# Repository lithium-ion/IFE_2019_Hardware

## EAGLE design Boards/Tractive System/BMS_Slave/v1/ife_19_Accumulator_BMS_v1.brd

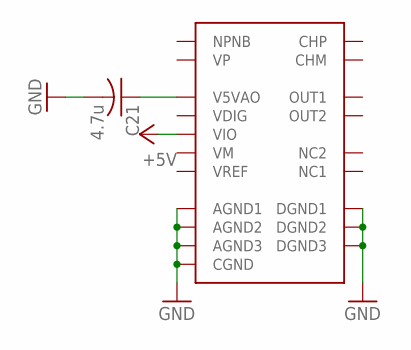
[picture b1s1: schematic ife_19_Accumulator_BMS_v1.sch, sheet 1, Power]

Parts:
C21: 4.7u; C0805
U$1: BQ76PL455A; TQFP80

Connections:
+5V: U$1.41 (VIO); also elsewhere on the board
GND: C21.2, U$1.30 (DGND1), U$1.35 (DGND2), U$1.37 (DGND3), U$1.48 (CGND), U$1.69 (AGND3), U$1.72 (AGND2), U$1.74 (AGND1); also elsewhere on the board
unnamed: C21.1, U$1.58 (V5VAO)

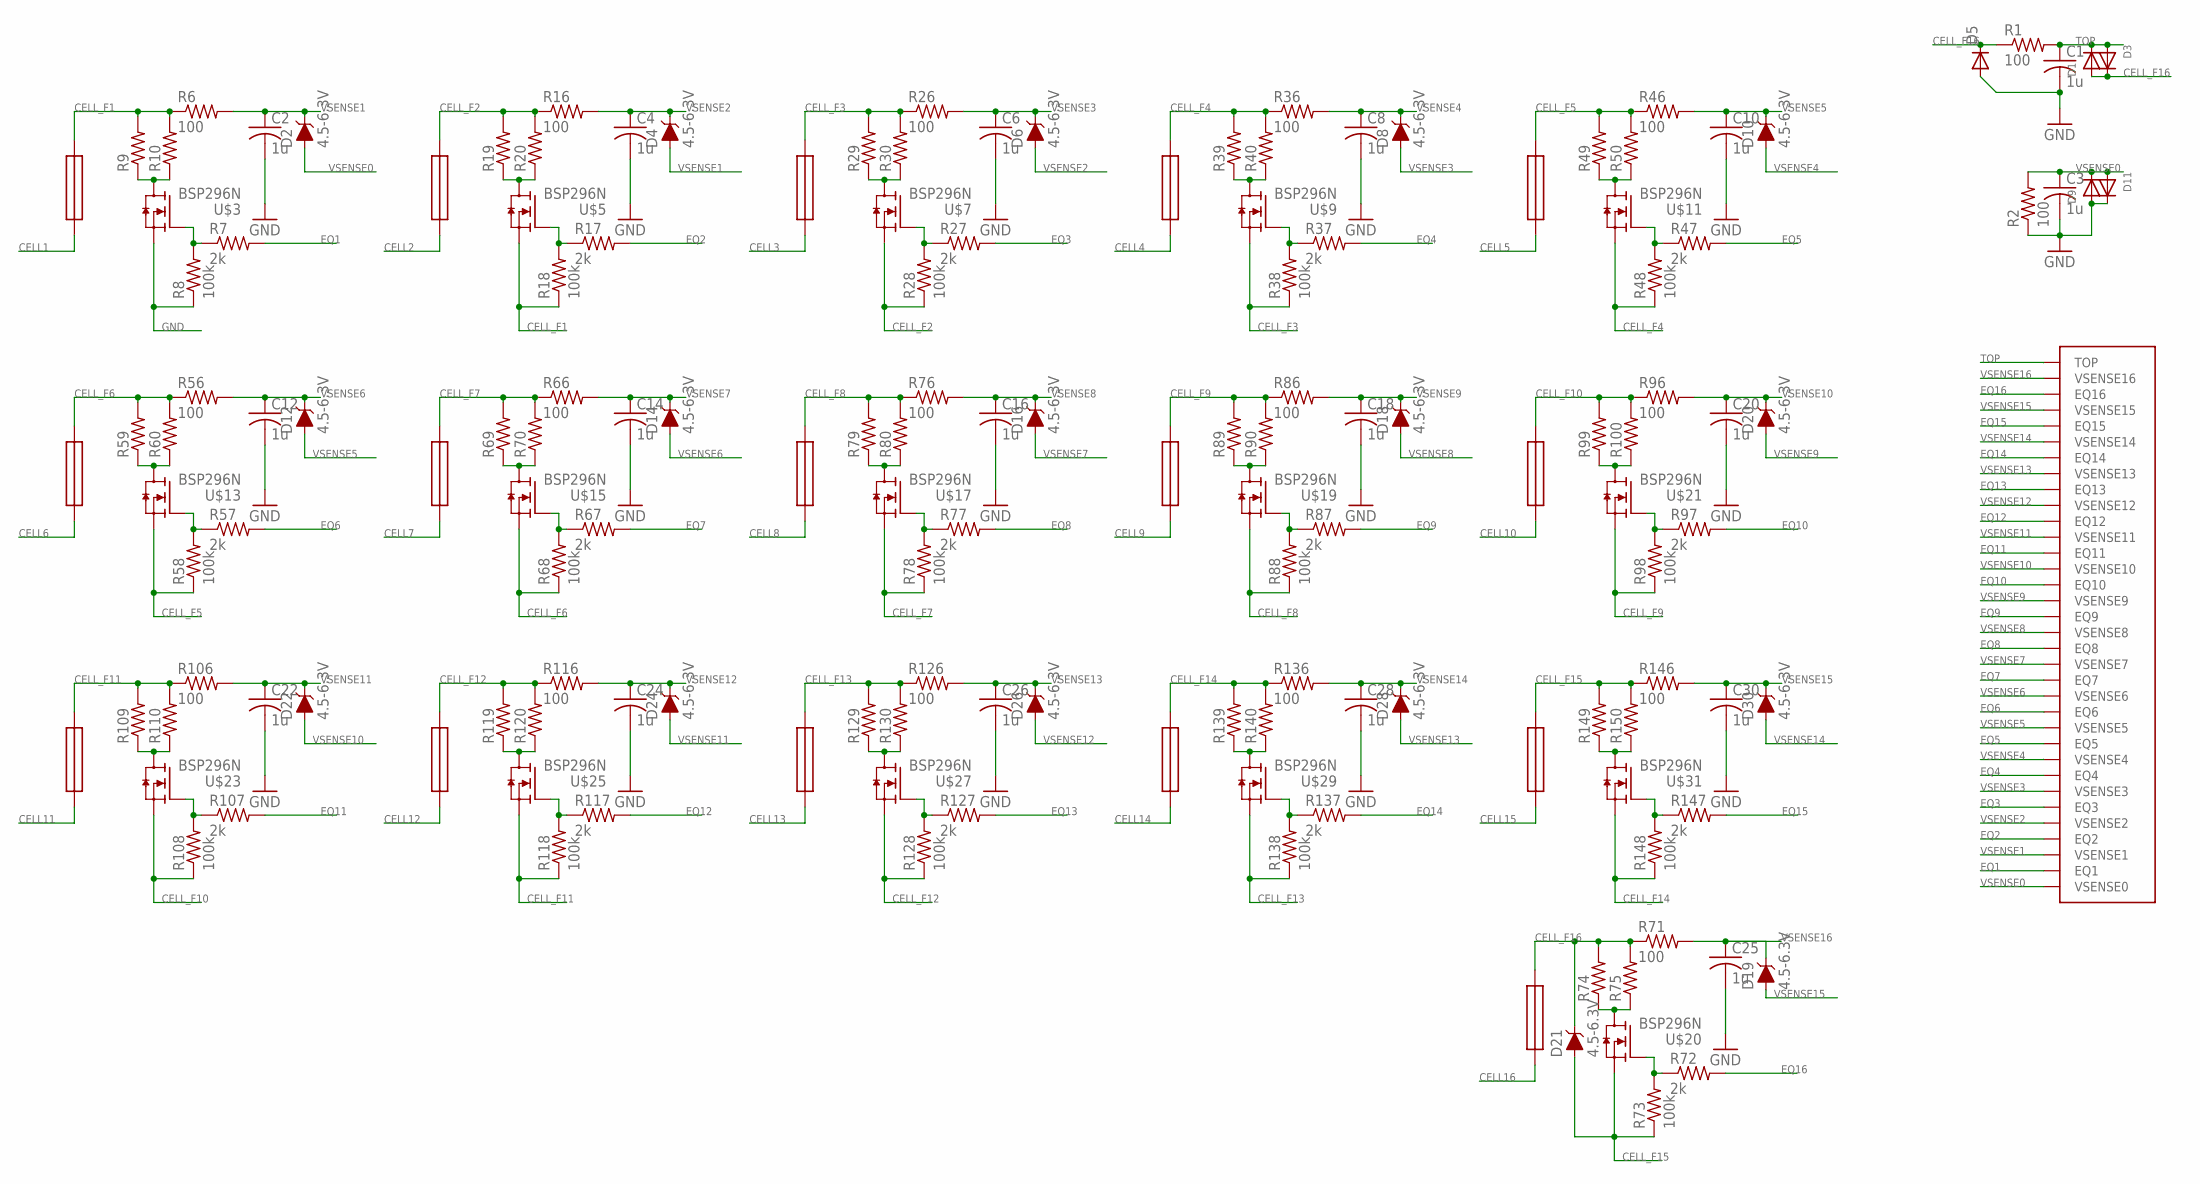
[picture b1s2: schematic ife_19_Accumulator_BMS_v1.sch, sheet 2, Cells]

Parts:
C1, C2, C3, C4, C6, C8, C10, C12, C14, C16, C18, C20, C22, C24, C25, C26, C28, C30: 1u; C0603K
D1, D3, D9, D11: DIODESOD-123; SOD-123
D2, D4, D6, D8, D10, D12, D14, D16, D18, D19, D20, D21, D22, D24, D26, D28, D30: 4.5-6.3V; SOD-323
D5: DIODE-DO214AC; DO214AC
FUSE1, FUSE2, FUSE3, FUSE5, FUSE7, FUSE9, FUSE11, FUSE13, FUSE15, FUSE17, FUSE19, FUSE21, FUSE23, FUSE25, FUSE27, FUSE29: 2A; 0.36"X0.15"
R1, R2, R6, R16, R26, R36, R46, R56, R66, R71, R76, R86, R96, R106, R116, R126, R136, R146: 100; R0603
R7, R17, R27, R37, R47, R57, R67, R72, R77, R87, R97, R107, R117, R127, R137, R147: 2k; R0603
R8, R18, R28, R38, R48, R58, R68, R73, R78, R88, R98, R108, R118, R128, R138, R148: 100k; R0603
R9, R10, R19, R20, R29, R30, R39, R40, R49, R50, R59, R60, R69, R70, R74, R75, R79, R80, R89, R90, R99, R100, R109, R110, R119, R120, R129, R130, R139, R140, R149, R150: R-US_R2512; R2512
U$1: BQ76PL455A; TQFP80
U$3, U$5, U$7, U$9, U$11, U$13, U$15, U$17, U$19, U$20, U$21, U$23, U$25, U$27, U$29, U$31: BSP296N; PG-SOT-223

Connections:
CELL1: FUSE1.P$1
CELL2: FUSE3.P$1
CELL3: FUSE5.P$1
CELL4: FUSE7.P$1
CELL5: FUSE9.P$1
CELL6: FUSE11.P$1
CELL7: FUSE13.P$1
CELL8: FUSE15.P$1
CELL9: FUSE17.P$1
CELL10: FUSE19.P$1
CELL11: FUSE21.P$1
CELL12: FUSE23.P$1
CELL13: FUSE25.P$1
CELL14: FUSE27.P$1
CELL15: FUSE29.P$1
CELL16: FUSE2.P$1
CELL_F1: FUSE1.P$2, R6.1, R9.2, R10.2, R18.1, U$5.3 (S)
CELL_F2: FUSE3.P$2, R16.1, R19.2, R20.2, R28.1, U$7.3 (S)
CELL_F3: FUSE5.P$2, R26.1, R29.2, R30.2, R38.1, U$9.3 (S)
CELL_F4: FUSE7.P$2, R36.1, R39.2, R40.2, R48.1, U$11.3 (S)
CELL_F5: FUSE9.P$2, R46.1, R49.2, R50.2, R58.1, U$13.3 (S)
CELL_F6: FUSE11.P$2, R56.1, R59.2, R60.2, R68.1, U$15.3 (S)
CELL_F7: FUSE13.P$2, R66.1, R69.2, R70.2, R78.1, U$17.3 (S)
CELL_F8: FUSE15.P$2, R76.1, R79.2, R80.2, R88.1, U$19.3 (S)
CELL_F9: FUSE17.P$2, R86.1, R89.2, R90.2, R98.1, U$21.3 (S)
CELL_F10: FUSE19.P$2, R96.1, R99.2, R100.2, R108.1, U$23.3 (S)
CELL_F11: FUSE21.P$2, R106.1, R109.2, R110.2, R118.1, U$25.3 (S)
CELL_F12: FUSE23.P$2, R116.1, R119.2, R120.2, R128.1, U$27.3 (S)
CELL_F13: FUSE25.P$2, R126.1, R129.2, R130.2, R138.1, U$29.3 (S)
CELL_F14: FUSE27.P$2, R136.1, R139.2, R140.2, R148.1, U$31.3 (S)
CELL_F15: D21.A, FUSE29.P$2, R73.1, R146.1, R149.2, R150.2, U$20.3 (S)
CELL_F16: D1.A, D3.C, D5.C, D21.C, FUSE2.P$2, R1.1, R71.1, R74.2, R75.2
EQ1: R7.2, U$1.28 (EQ1)
EQ2: R17.2, U$1.26 (EQ2)
EQ3: R27.2, U$1.24 (EQ3)
EQ4: R37.2, U$1.22 (EQ4)
EQ5: R47.2, U$1.20 (EQ5)
EQ6: R57.2, U$1.18 (EQ6)
EQ7: R67.2, U$1.16 (EQ7)
EQ8: R77.2, U$1.14 (EQ8)
EQ9: R87.2, U$1.12 (EQ9)
EQ10: R97.2, U$1.10 (EQ10)
EQ11: R107.2, U$1.8 (EQ11)
EQ12: R117.2, U$1.6 (EQ12)
EQ13: R127.2, U$1.4 (EQ13)
EQ14: R137.2, U$1.2 (EQ14)
EQ15: R147.2, U$1.80 (EQ15)
EQ16: R72.2, U$1.78 (EQ16)
GATE1: R7.1, R8.2, U$3.1 (G)
GATE2: R17.1, R18.2, U$5.1 (G)
GATE3: R27.1, R28.2, U$7.1 (G)
GATE4: R37.1, R38.2, U$9.1 (G)
GATE5: R47.1, R48.2, U$11.1 (G)
GATE6: R57.1, R58.2, U$13.1 (G)
GATE7: R67.1, R68.2, U$15.1 (G)
GATE8: R77.1, R78.2, U$17.1 (G)
GATE9: R87.1, R88.2, U$19.1 (G)
GATE10: R97.1, R98.2, U$21.1 (G)
GATE11: R107.1, R108.2, U$23.1 (G)
GATE12: R117.1, R118.2, U$25.1 (G)
GATE13: R127.1, R128.2, U$27.1 (G)
GATE14: R137.1, R138.2, U$29.1 (G)
GATE15: R147.1, R148.2, U$31.1 (G)
GATE16: R72.1, R73.2, U$20.1 (G)
GND: C1.2, C2.2, C3.2, C4.2, C6.2, C8.2, C10.2, C12.2, C14.2, C16.2, C18.2, C20.2, C22.2, C24.2, C25.2, C26.2, C28.2, C30.2, D5.A, D9.A, D11.C, R2.1, R8.1, U$3.3 (S); also elsewhere on the board
unnamed: R9.1, R10.1, U$3.2 (D), U$3.4 (D)
unnamed: R19.1, R20.1, U$5.2 (D), U$5.4 (D)
unnamed: R29.1, R30.1, U$7.2 (D), U$7.4 (D)
unnamed: R39.1, R40.1, U$9.2 (D), U$9.4 (D)
unnamed: R49.1, R50.1, U$11.2 (D), U$11.4 (D)
unnamed: R59.1, R60.1, U$13.2 (D), U$13.4 (D)
unnamed: R74.1, R75.1, U$20.2 (D), U$20.4 (D)
unnamed: R69.1, R70.1, U$15.2 (D), U$15.4 (D)
unnamed: R79.1, R80.1, U$17.2 (D), U$17.4 (D)
unnamed: R89.1, R90.1, U$19.2 (D), U$19.4 (D)
unnamed: R99.1, R100.1, U$21.2 (D), U$21.4 (D)
unnamed: R109.1, R110.1, U$23.2 (D), U$23.4 (D)
unnamed: R119.1, R120.1, U$25.2 (D), U$25.4 (D)
unnamed: R129.1, R130.1, U$27.2 (D), U$27.4 (D)
unnamed: R139.1, R140.1, U$29.2 (D), U$29.4 (D)
unnamed: R149.1, R150.1, U$31.2 (D), U$31.4 (D)
TOP: C1.1, D1.C, D3.A, R1.2, U$1.76 (TOP)
VSENSE0: C3.1, D2.A, D9.C, D11.A, R2.2, U$1.29 (VSENSE0)
VSENSE1: C2.1, D2.C, D4.A, R6.2, U$1.27 (VSENSE1)
VSENSE2: C4.1, D4.C, D6.A, R16.2, U$1.25 (VSENSE2)
VSENSE3: C6.1, D6.C, D8.A, R26.2, U$1.23 (VSENSE3)
VSENSE4: C8.1, D8.C, D10.A, R36.2, U$1.21 (VSENSE4)
VSENSE5: C10.1, D10.C, D12.A, R46.2, U$1.19 (VSENSE5)
VSENSE6: C12.1, D12.C, D14.A, R56.2, U$1.17 (VSENSE6)
VSENSE7: C14.1, D14.C, D16.A, R66.2, U$1.15 (VSENSE7)
VSENSE8: C16.1, D16.C, D18.A, R76.2, U$1.13 (VSENSE8)
VSENSE9: C18.1, D18.C, D20.A, R86.2, U$1.11 (VSENSE9)
VSENSE10: C20.1, D20.C, D22.A, R96.2, U$1.9 (VSENSE10)
VSENSE11: C22.1, D22.C, D24.A, R106.2, U$1.7 (VSENSE11)
VSENSE12: C24.1, D24.C, D26.A, R116.2, U$1.5 (VSENSE12)
VSENSE13: C26.1, D26.C, D28.A, R126.2, U$1.3 (VSENSE13)
VSENSE14: C28.1, D28.C, D30.A, R136.2, U$1.1 (VSENSE14)
VSENSE15: C30.1, D19.A, D30.C, R146.2, U$1.79 (VSENSE15)
VSENSE16: C25.1, D19.C, R71.2, U$1.77 (VSENSE16)

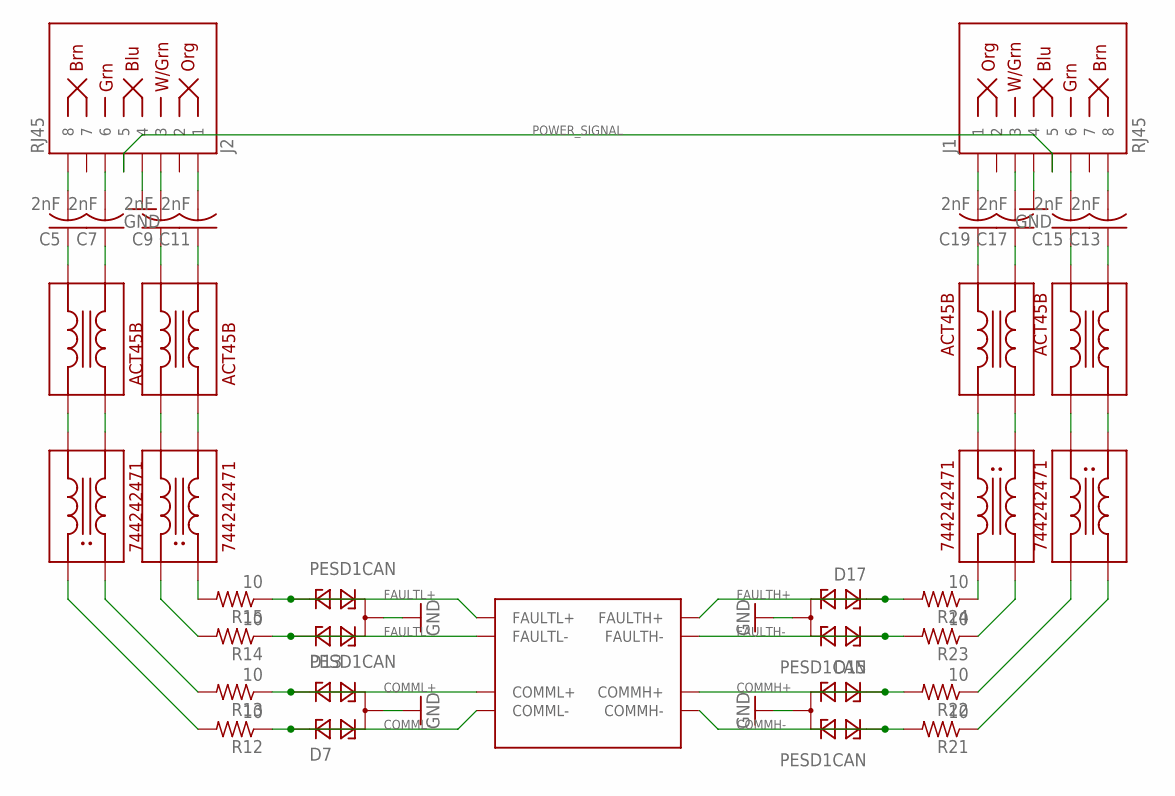
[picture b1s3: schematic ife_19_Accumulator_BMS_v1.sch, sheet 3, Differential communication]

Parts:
C5, C7, C9, C11, C13, C15, C17, C19: 2nF; C0805
D7, D13, D15, D17: PESD1CAN; SOT23
J1, J2: RJ45; RJ45-8
R12, R13, R14, R15, R21, R22, R23, R24: 10; R0805
U$1: BQ76PL455A; TQFP80
U$2, U$4, U$6, U$8: ACT45B; 1812-4
U$10, U$12, U$14, U$16: WURTH-744242471; 744242471

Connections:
COMMH+: D15.1, R22.2, U$1.55 (COMMH+)
COMMH-: D15.2, R21.2, U$1.54 (COMMH-)
COMML+: D7.2, R13.1, U$1.52 (COMML+)
COMML-: D7.1, R12.1, U$1.53 (COMML-)
FAULTH+: D17.1, R24.2, U$1.57 (FAULTH+)
FAULTH-: D17.2, R23.2, U$1.56 (FAULTH-)
FAULTL+: D13.2, R15.1, U$1.50 (FAULTL+)
FAULTL-: D13.1, R14.1, U$1.51 (FAULTL-)
GND: D7.3, D13.3, D15.3, D17.3, J1.4, J2.4; also elsewhere on the board
unnamed: C5.1, U$6.P$4
unnamed: C7.1, U$6.P$3
unnamed: C9.1, U$8.P$4
unnamed: C11.1, U$8.P$3
unnamed: C13.1, U$2.P$2
unnamed: C15.1, U$2.P$1
unnamed: C17.1, U$4.P$2
unnamed: C19.1, U$4.P$1
unnamed: U$2.P$3, U$14.2
unnamed: U$2.P$4, U$14.1
unnamed: U$4.P$3, U$16.2
unnamed: U$4.P$4, U$16.1
unnamed: U$6.P$1, U$10.3
unnamed: U$6.P$2, U$10.4
unnamed: U$8.P$1, U$12.3
unnamed: U$8.P$2, U$12.4
unnamed: R14.2, U$12.1
unnamed: R13.2, U$10.2
unnamed: R12.2, U$10.1
unnamed: R15.2, U$12.2
unnamed: R23.1, U$16.4
unnamed: R22.1, U$14.3
unnamed: R21.1, U$14.4
unnamed: R24.1, U$16.3
unnamed: C5.2, J2.8
unnamed: C7.2, J2.6
unnamed: C9.2, J2.3
unnamed: C11.2, J2.1
unnamed: C13.2, J1.8
unnamed: C15.2, J1.6
unnamed: C17.2, J1.3
unnamed: C19.2, J1.1
POWER_SIGNAL: J1.5, J2.5

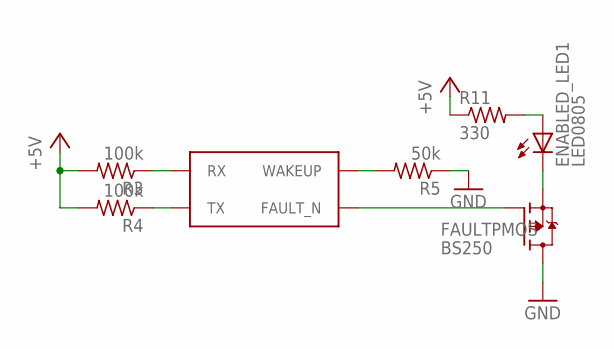
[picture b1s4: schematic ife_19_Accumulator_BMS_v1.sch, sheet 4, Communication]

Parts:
ENABLED_LED1: LED0805
FAULTPMOS: BS250; SOT23
R3, R4: 100k; R0805
R5: 50k; R0805
R11: 330; R0805
U$1: BQ76PL455A; TQFP80

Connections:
+5V: R3.2, R4.2, R11.1; also elsewhere on the board
FAULT_N: FAULTPMOS.1 (G), U$1.40 (FAULT_N)
GND: FAULTPMOS.3 (D), R5.1; also elsewhere on the board
unnamed: ENABLED_LED1.2 (C), FAULTPMOS.2 (S)
unnamed: ENABLED_LED1.1 (A), R11.2
RX: R3.1, U$1.39 (RX)
TX: R4.1, U$1.38 (TX)
WAKEUP: R5.2, U$1.49 (WAKEUP)

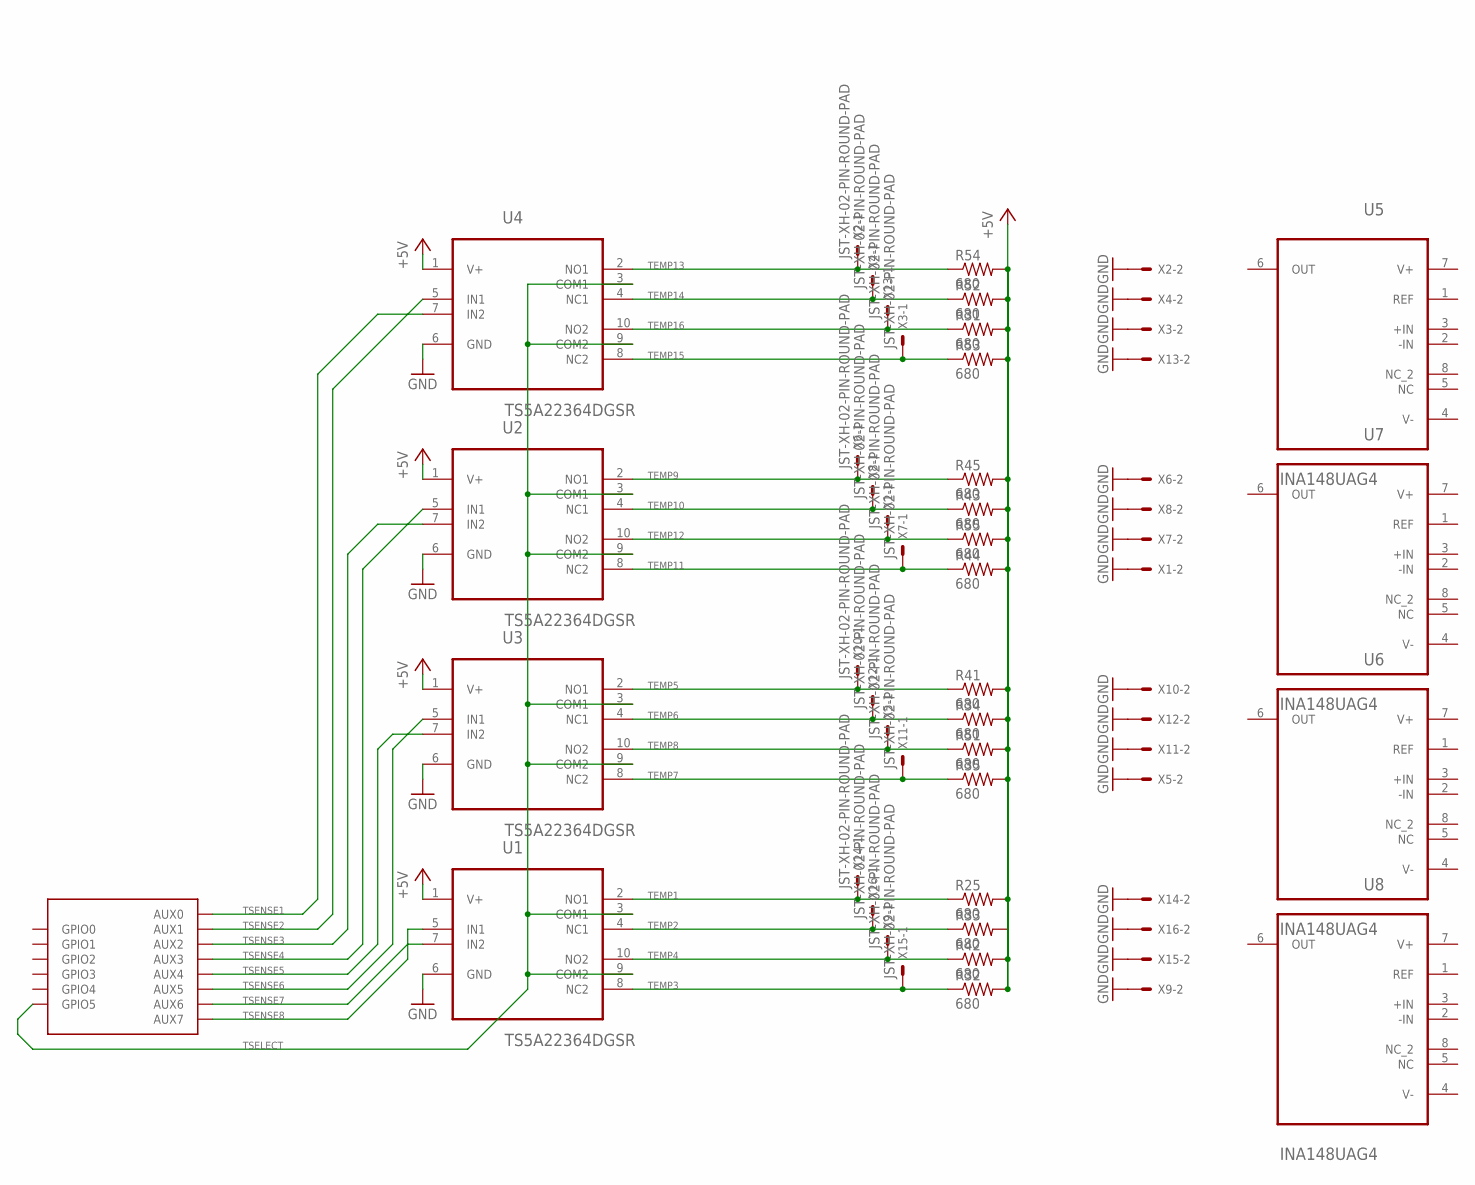
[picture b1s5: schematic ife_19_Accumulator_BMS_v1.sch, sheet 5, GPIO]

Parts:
R25, R31, R32, R33, R34, R35, R41, R42, R43, R44, R45, R51, R52, R53, R54, R55: 680; R0805
U1, U2, U3, U4: TS5A22364DGSR; SOP50P490X110-10N
U5, U6, U7, U8: INA148UAG4; SOIC127P600X175-8N
U$1: BQ76PL455A; TQFP80
X1, X2, X3, X4, X5, X6, X7, X8, X9, X10, X11, X12, X13, X14, X15, X16: JST-XH-02-PIN-ROUND-PAD; JST-XH-02-PACKAGE-ROUND-PAD

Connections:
+5V: R25.2, R31.2, R32.2, R33.2, R34.2, R35.2, R41.2, R42.2, R43.2, R44.2, R45.2, R51.2, R52.2, R53.2, R54.2, R55.2, U1.1 (V+), U2.1 (V+), U3.1 (V+), U4.1 (V+); also elsewhere on the board
GND: U1.6 (GND), U2.6 (GND), U3.6 (GND), U4.6 (GND), X1.2, X2.2, X3.2, X4.2, X5.2, X6.2, X7.2, X8.2, X9.2, X10.2, X11.2, X12.2, X13.2, X14.2, X15.2, X16.2; also elsewhere on the board
TEMP1: R25.1, U1.2 (NO1), X14.1
TEMP2: R33.1, U1.4 (NC1), X16.1
TEMP3: R32.1, U1.8 (NC2), X15.1
TEMP4: R42.1, U1.10 (NO2), X9.1
TEMP5: R41.1, U3.2 (NO1), X10.1
TEMP6: R34.1, U3.4 (NC1), X12.1
TEMP7: R35.1, U3.8 (NC2), X11.1
TEMP8: R51.1, U3.10 (NO2), X5.1
TEMP9: R45.1, U2.2 (NO1), X6.1
TEMP10: R43.1, U2.4 (NC1), X8.1
TEMP11: R44.1, U2.8 (NC2), X7.1
TEMP12: R55.1, U2.10 (NO2), X1.1
TEMP13: R54.1, U4.2 (NO1), X2.1
TEMP14: R52.1, U4.4 (NC1), X4.1
TEMP15: R53.1, U4.8 (NC2), X3.1
TEMP16: R31.1, U4.10 (NO2), X13.1
TSELECT: U1.3 (COM1), U1.9 (COM2), U2.3 (COM1), U2.9 (COM2), U3.3 (COM1), U3.9 (COM2), U4.3 (COM1), U4.9 (COM2), U$1.42 (GPIO5)
TSENSE1: U4.7 (IN2), U$1.66 (AUX0)
TSENSE2: U4.5 (IN1), U$1.65 (AUX1)
TSENSE3: U2.7 (IN2), U$1.64 (AUX2)
TSENSE4: U2.5 (IN1), U$1.63 (AUX3)
TSENSE5: U3.7 (IN2), U$1.62 (AUX4)
TSENSE6: U3.5 (IN1), U$1.61 (AUX5)
TSENSE7: U1.7 (IN2), U$1.60 (AUX6)
TSENSE8: U1.5 (IN1), U$1.59 (AUX7)
V+: U5.7 (V+), U6.7 (V+), U7.7 (V+), U8.7 (V+)
V-: U5.4 (V-), U6.4 (V-), U7.4 (V-), U8.4 (V-)

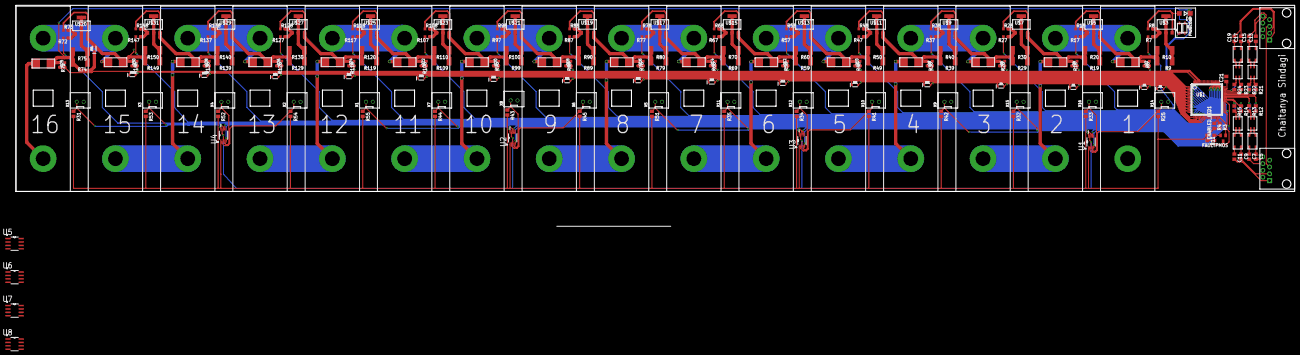
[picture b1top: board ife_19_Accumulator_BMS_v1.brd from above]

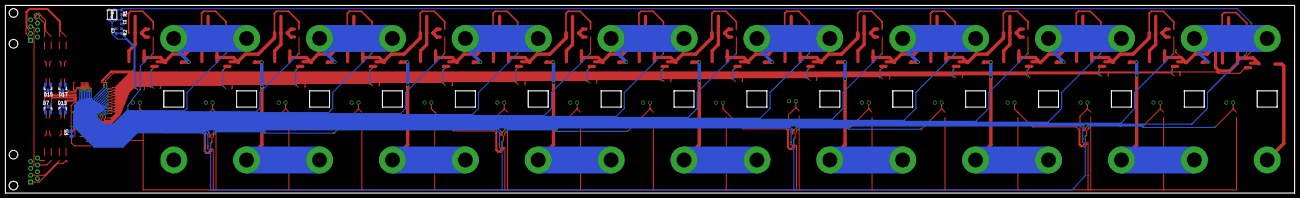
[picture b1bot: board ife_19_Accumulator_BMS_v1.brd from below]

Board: 2 copper layers, 477.5 x 69.5 mm, 232 parts (11 on the bottom side), 159 nets.

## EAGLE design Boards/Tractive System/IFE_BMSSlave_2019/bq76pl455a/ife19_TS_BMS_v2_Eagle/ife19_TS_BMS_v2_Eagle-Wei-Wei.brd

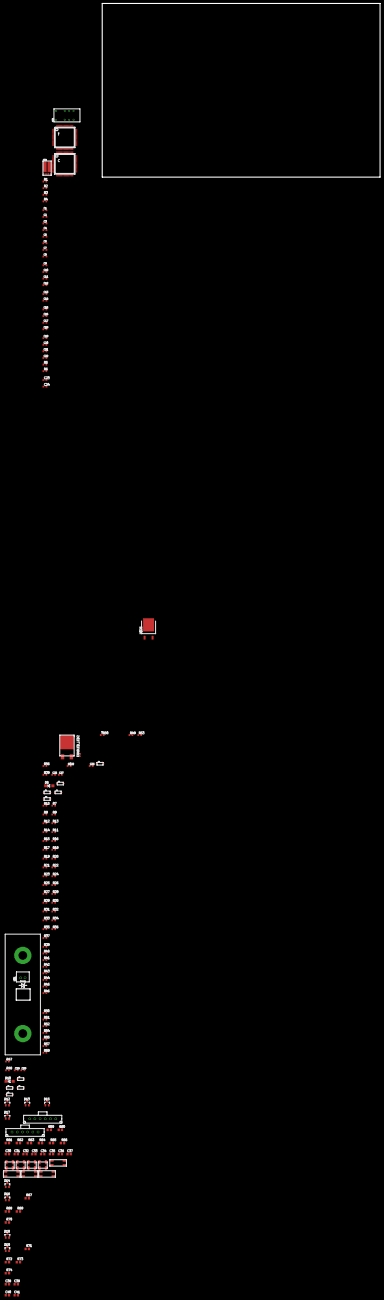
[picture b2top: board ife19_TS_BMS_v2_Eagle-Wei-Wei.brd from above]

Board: 2 copper layers, 154 parts (0 on the bottom side), 133 nets, no tracks yet.

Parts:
C: BQ76PL455A; TQFP80
C1, C2: 390p; C0603K
C3, C4, C9, C11, C15, C17, C20, C21: 4.7u; C0603K
C5, C7, C10, C12, C13, C14, C16, C19, C22: 0.1u; C0603K
C6, C8: 1.8u; C0603K
C18: 0.1; C0603K
C23, C24: 22n; C0603
C25, C26, C27, C28, C29: 1u; C0603K
C30, C31, C32, C33, C34, C35, C36, C37, C38, C39, C40, C41: 1nF; C0805
D1, D2, D3, D4, D6, D7, D8, D9, D11: SOD-123
D5, D10: DO214AC
D12, D13, D14, D15, D16, D17, D18, D19: PESD1CAN; SOT23
ENABLED_LED2: CHIPLED_0603
R1, R2, R3, R4: 1; R0603
R5, R6: 0.39; R0603
R7, R8, R9, R10, R11, R12, R13, R14, R15, R16, R17, R18, R19, R20, R21, R22, R23, R24, R25, R26, R27, R28, R29, R30, R31, R32, R33, R34, R35, R36, R37, R39, R48, R49: 100; R0603
R38, R40, R41, R42, R43, R44, R45, R46, R50, R51, R52, R54, R55, R57, R58: 1k; R0603
R47, R56: 2k; R0603
R53: 330; R0603
R59, R60, R61, R62, R63, R64, R65, R66, R67, R68, R69, R70, R71, R72, R73, R74: 10; R0805
T: BQ76PL455A; TQFP80
TR50: 100K; R0603
U$1: LI6PT; 6PT
U$2, U$6, U$8, U$9: SRF5432
U$3: EC2; DPDT_2.54
U$4: PHPT610030NK; LFPAK56D
U$5, U$7: MICROFIT3.0-3P; 6POS-3MM
U$10, U$12, U$14, U$16: DR331
U$22: SF-0603FP; 0603
U$23: TKH45; TO252-TKH-45
U$25: IPD60N10S4L-12; TO252

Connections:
CELL15: R21.1, R37.2, R58.2, TR50.1, U$1.1, U$1.CELLH-, U$1.CELLP-, U$23.3, U$25.3
CELL16: R47.2, U$1.CELLH+, U$1.CELLP+, U$22.1
CELL_F16: D5.C, D10.C, R39.1, R48.1, R49.1, R53.1, U$22.2, U$23.1
COMMH+: D15.1, R64.2, T.55
COMMH+ISO: C35.2, U$7.P$2
COMMH-: D15.2, R63.2, T.54
COMMH-ISO: C34.2, U$7.P$1
COMML+: C.52, C.56, D12.2, D14.2, D18.2, R60.1, R68.1, R72.1, T.52
COMML+ISO: C31.2, U$5.P$5
COMML-: C.53, C.57, D12.1, D14.1, D18.1, R59.1, R67.1, R71.1, T.53
COMML-ISO: C30.2, U$5.P$6
C_CELL_EQ16: C.78, R56.1
C_CELL_TOP: C.76, C25.1, D1.C, D3.A, R39.2
C_CELL_VSENSE0: C.29, C27.1, D9.C, D11.A
C_CELL_VSENSE1: C.27, R23.1
C_CELL_VSENSE2: C.25, R24.1
C_CELL_VSENSE3: C.23, R25.1
C_CELL_VSENSE4: C.21, R26.1
C_CELL_VSENSE5: C.19, R27.1
C_CELL_VSENSE6: C.17, R28.1
C_CELL_VSENSE7: C.15, R29.1
C_CELL_VSENSE8: C.13, R30.1
C_CELL_VSENSE9: C.11, R31.1
C_CELL_VSENSE10: C.9, R32.1
C_CELL_VSENSE11: C.7, R33.1
C_CELL_VSENSE12: C.5, R34.1
C_CELL_VSENSE13: C.3, R35.1
C_CELL_VSENSE14: C.1, R36.1
C_CELL_VSENSE15: C.79, R37.1
C_CELL_VSENSE16: C.77, C26.1, D1.A, D2.C, D3.C, D4.A, D6.C, R49.2
FAULTH+: D17.1, R66.2, T.57
FAULTH+ISO: C37.2, U$7.P$4
FAULTH-: D17.2, R65.2, T.56
FAULTH-ISO: C36.2, U$7.P$3
FAULTL+: C.50, C.54, D13.2, D16.2, D19.2, R62.1, R70.1, R74.1, T.50
FAULTL+ISO: C33.2, U$5.P$3
FAULTL-: C.51, C.55, D13.1, D16.1, D19.1, R61.1, R69.1, R73.1, T.51
FAULTL-ISO: C32.2, U$5.P$4
GATE16: R56.2, TR50.2, U$25.1
GND: C.30, C.35, C.37, C.48, C.69, C.72, C.74, C1.2, C2.2, C3.2, C4.2, C5.2, C6.2, C7.2, C8.2, C9.2, C10.2, C11.2, C12.2, C13.2, C14.2, C15.2, C16.2, C17.2, C18.2, C19.2, C20.2, C21.2, C22.2, C25.2, C26.2, C27.2, C28.2, C29.2, D5.A, D7.A, D8.C, D9.A, D10.A, D11.C, D12.3, D13.3, D14.3, D15.3, D16.3, D17.3, D18.3, D19.3, R38.1, T.30, T.35, T.37, T.48, T.69, T.72, T.74
unnamed: C.32, C23.1
unnamed: C.33, C23.2
unnamed: C.68, C.73, C1.1
unnamed: C2.1, T.68, T.73
unnamed: C24.1, T.32
unnamed: C24.2, T.33
unnamed: R3.2, U$3.$P8
unnamed: R4.2, U$3.$P5
unnamed: C30.1, U$2.P$3
unnamed: C31.1, U$2.P$2
unnamed: R20.1, R36.2, R46.2, R58.1
unnamed: R19.1, R35.2, R46.1, R57.2
unnamed: R18.1, R34.2, R45.2, R57.1
unnamed: R17.1, R33.2, R45.1, R55.2
unnamed: R16.1, R32.2, R44.2, R55.1
unnamed: R15.1, R31.2, R44.1, R54.2
unnamed: R14.1, R30.2, R43.2, R54.1
unnamed: R13.1, R29.2, R43.1, R52.2
unnamed: R12.1, R28.2, R42.2, R52.1
unnamed: C20.1, R5.1
unnamed: C21.1, R6.1
unnamed: R11.1, R27.2, R42.1, R51.2
unnamed: R10.1, R26.2, R41.2, R51.1
unnamed: R9.1, R25.2, R41.1, R50.2
unnamed: R8.1, R24.2, R40.2, R50.1
unnamed: R7.1, R23.2, R38.2, R40.1
unnamed: C32.1, U$6.P$3
unnamed: C33.1, U$6.P$2
unnamed: ENABLED_LED2.A, R53.2
unnamed: C34.1, U$9.P$2
unnamed: C35.1, U$9.P$3
unnamed: C36.1, U$8.P$2
unnamed: C37.1, U$8.P$3
unnamed: U$9.P$4, U$14.P$2
unnamed: U$9.P$1, U$14.P$1
unnamed: U$8.P$4, U$16.P$2
unnamed: U$8.P$1, U$16.P$1
unnamed: U$2.P$1, U$10.P$3
unnamed: U$2.P$4, U$10.P$4
unnamed: U$6.P$1, U$12.P$3
unnamed: ENABLED_LED2.C, U$23.2, U$25.2
unnamed: U$6.P$4, U$12.P$4
unnamed: R62.2, U$12.P$2
unnamed: R66.1, U$16.P$3
unnamed: R61.2, U$12.P$1
unnamed: R60.2, U$10.P$2
unnamed: R59.2, U$10.P$1
unnamed: R65.1, U$16.P$4
unnamed: R64.1, U$14.P$3
unnamed: R63.1, U$14.P$4
unnamed: C41.2, R67.2
unnamed: C40.2, R68.2
unnamed: C39.2, R69.2
unnamed: C38.2, R70.2
unnamed: C38.1, R71.2
unnamed: C39.1, R72.2
unnamed: C40.1, R73.2
unnamed: C41.1, R74.2
NPNB_C: C.71, U$4.B1
NPNB_T: T.71, U$4.B2
ON+: U$3.$P12, U$5.P$1, U$7.P$6
ON-: U$3.$P1, U$5.P$2, U$7.P$5
TOP: U$4.C1, U$4.C2
T_CELL_TOP: C28.1, D4.C, D6.A, R48.2, T.76
T_CELL_VSENSE0: C29.1, D7.C, D8.A, T.29
T_CELL_VSENSE1: R7.2, T.27
T_CELL_VSENSE2: R8.2, T.25
T_CELL_VSENSE3: R9.2, T.23
T_CELL_VSENSE4: R10.2, T.21
T_CELL_VSENSE5: R11.2, T.19
T_CELL_VSENSE6: R12.2, T.17
T_CELL_VSENSE7: R13.2, T.15
T_CELL_VSENSE8: R14.2, T.13
T_CELL_VSENSE9: R15.2, T.11
T_CELL_VSENSE10: R16.2, T.9
T_CELL_VSENSE11: R17.2, T.7
T_CELL_VSENSE12: R18.2, T.5
T_CELL_VSENSE13: R19.2, T.3
T_CELL_VSENSE14: R20.2, T.1
T_CELL_VSENSE15: R21.2, T.79
T_CELL_VSENSE16: R22.2, R47.1, T.77, U$1.2
V5VAO_C: C.58, C3.1
V5VAO_T: C4.1, T.58
VDIG_C: C.34, C15.1, C16.1, R1.1
VDIG_T: C17.1, C18.1, R2.1, T.34
VIO_C: C.41, C13.1, R3.1
VIO_T: C14.1, R4.1, T.41
VM_C: C.31, C9.1, C10.1
VM_T: C11.1, C12.1, T.31
VP_C: C.70, C19.1, R1.2, R5.2, U$3.$P9, U$4.E1
VP_T: C22.1, R2.2, R6.2, T.70, U$3.$P4, U$4.E2
VREF_C: C.67, C5.1, C6.1
VREF_T: C7.1, C8.1, T.67

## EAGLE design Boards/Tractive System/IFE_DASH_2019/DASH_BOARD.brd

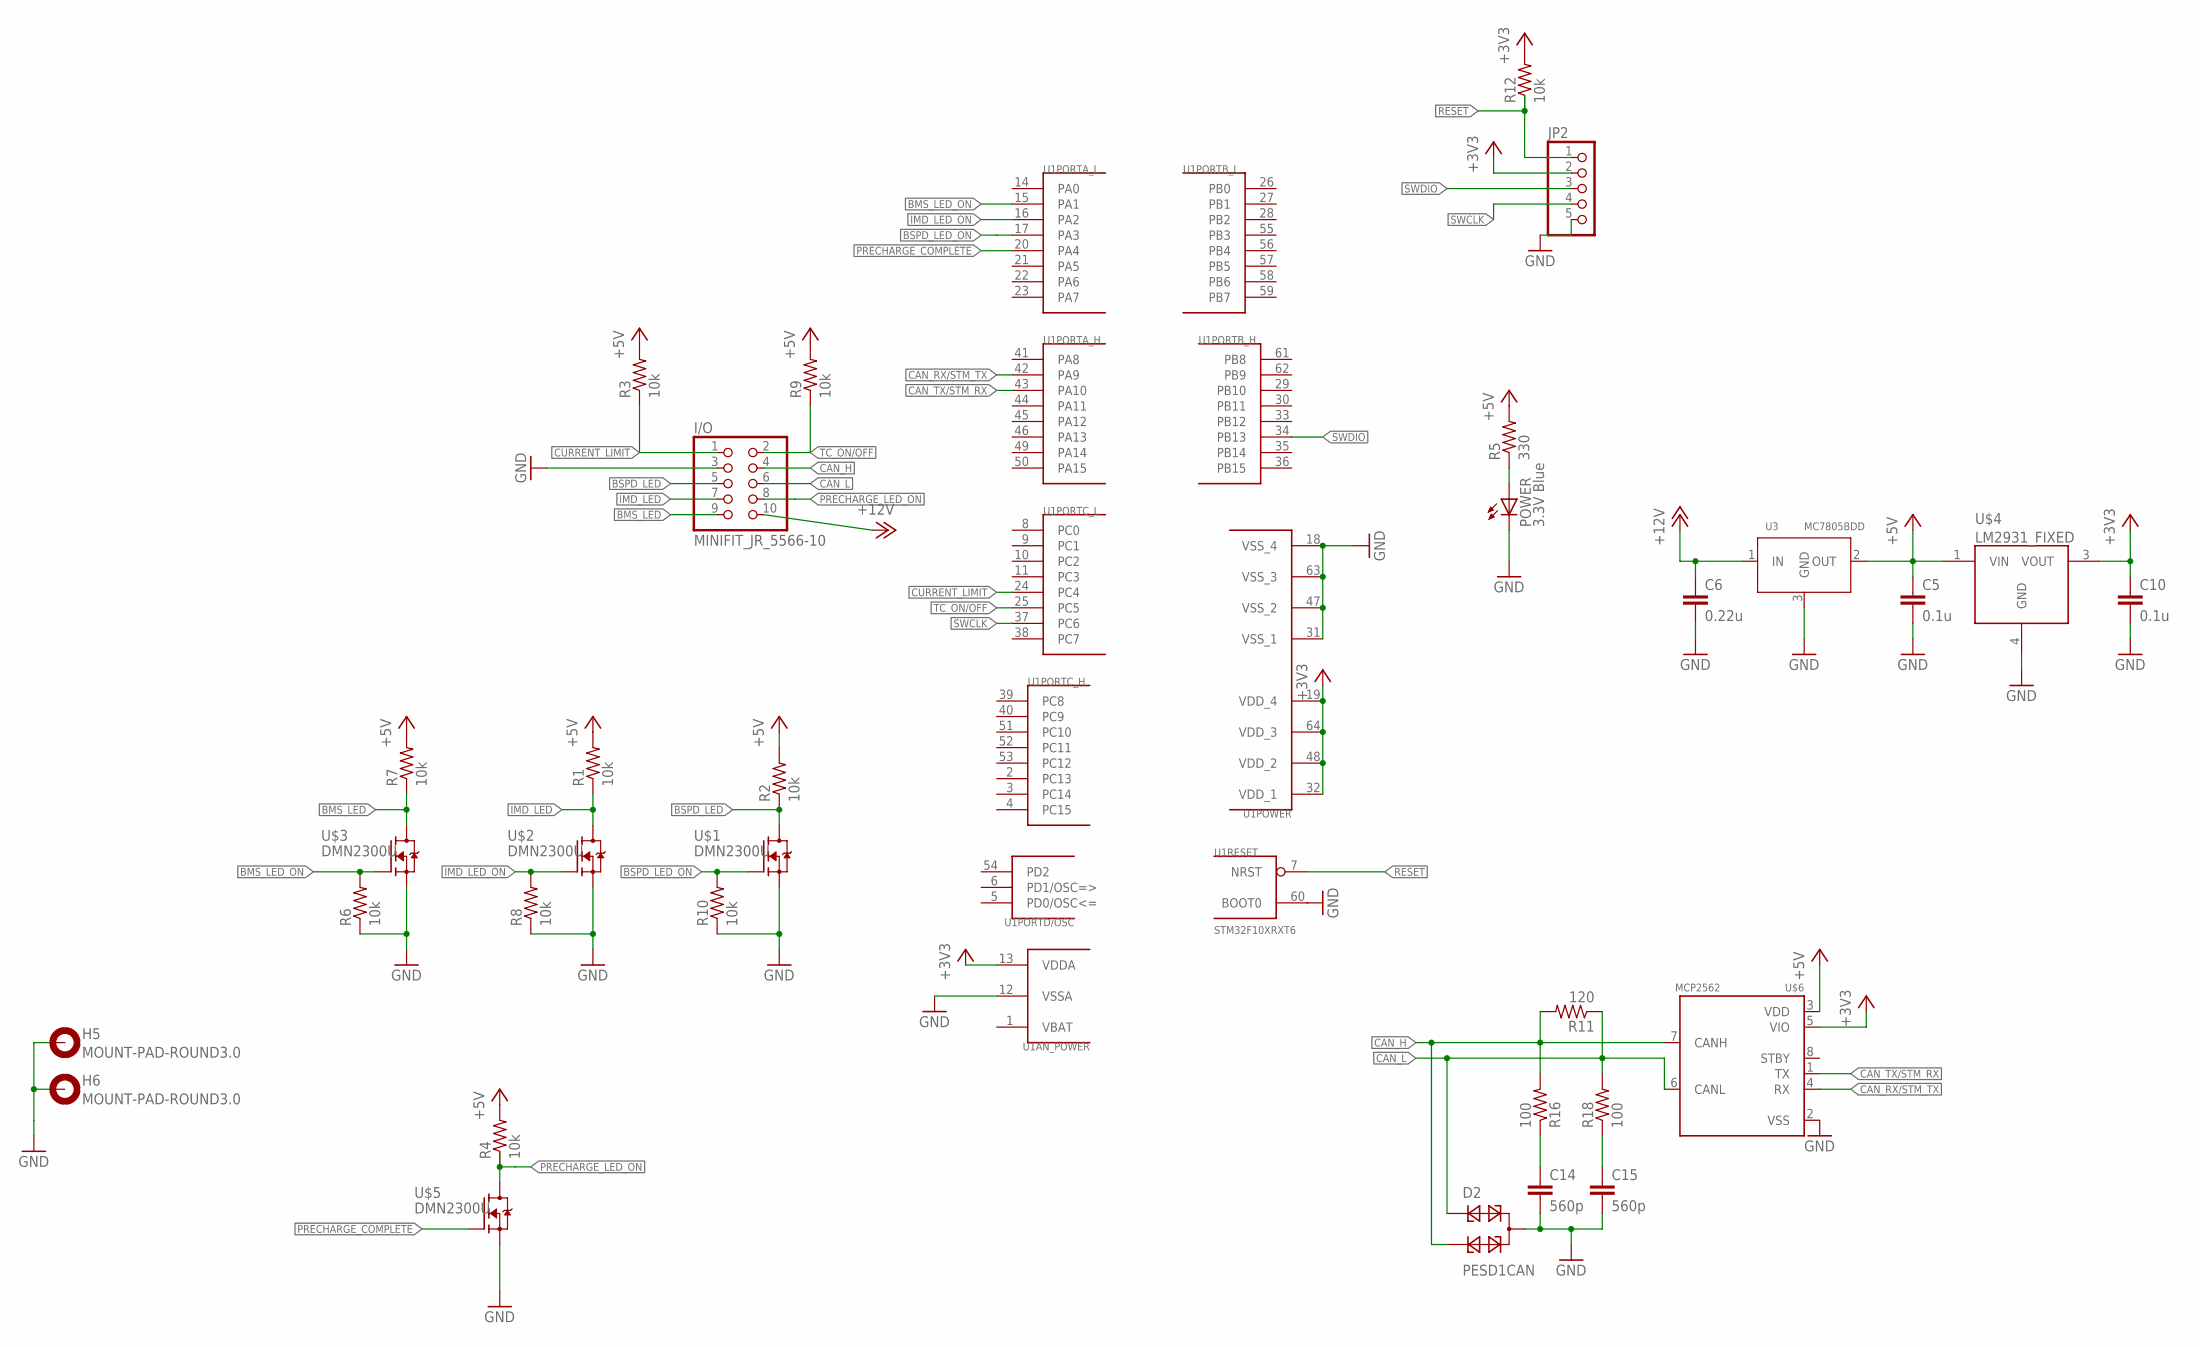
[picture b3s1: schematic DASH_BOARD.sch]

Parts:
C5, C10: 0.1u; C0805K
C6: 0.22u; C0805K
C14, C15: 560p; C0805K
D2: PESD1CAN; SOT23
H5, H6: MOUNT-PAD-ROUND3.0; 3,0-PAD
I/O: MINIFIT_JR_5566-10
JP2: PINHD-1X5; 1X05
POWER: 3.3V Blue; SML0805
R1, R2, R3, R4, R6, R7, R8, R9, R10, R12: 10k; R0805
R5: 330; R0805
R11: 120; R0805
R16, R18: 100; R0805
U1: STM32F10XRXT6; TQFP64
U3: MC7805BDD; DPAK
U$1, U$2, U$3, U$5: DMN2300U; SOT23
U$4: LM2931_FIXED; DPAK
U$6: MCP2562; SOIC8

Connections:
+3V3: C10.1, JP2.2, R12.2, U1.13 (VDDA), U1.19 (VDD_4), U1.32 (VDD_1), U1.48 (VDD_2), U1.64 (VDD_3), U$4.3 (VOUT), U$6.5 (VIO)
+5V: C5.1, R1.2, R2.2, R3.2, R4.2, R5.2, R7.2, R9.2, U3.2 (OUT), U$4.1 (VIN), U$6.3 (VDD)
+12V: C6.1, I/O.10, U3.1 (IN)
BMS_LED: I/O.9, R7.1, U$3.3 (D)
BMS_LED_ON: R6.2, U1.15 (PA1), U$3.1 (G)
BSPD_LED: I/O.5, R2.1, U$1.3 (D)
BSPD_LED_ON: R10.2, U1.17 (PA3), U$1.1 (G)
CAN_H: D2.2, I/O.4, R11.2, R16.2, U$6.7 (CANH)
CAN_L: D2.1, I/O.6, R11.1, R18.2, U$6.6 (CANL)
CAN_RX/STM_TX: U1.42 (PA9), U$6.4 (RX)
CAN_TX/STM_RX: U1.43 (PA10), U$6.1 (TX)
CURRENT_LIMIT: I/O.1, R3.1, U1.24 (PC4)
GND: C5.2, C6.2, C10.2, C14.2, C15.2, D2.3, H5.B3,0, H6.B3,0, I/O.3, JP2.5, POWER.C, R6.1, R8.1, R10.1, U1.12 (VSSA), U1.18 (VSS_4), U1.31 (VSS_1), U1.47 (VSS_2), U1.60 (BOOT0), U1.63 (VSS_3), U3.3 (GND), U$1.2 (S), U$2.2 (S), U$3.2 (S), U$4.4 (GND), U$5.2 (S), U$6.2 (VSS)
IMD_LED: I/O.7, R1.1, U$2.3 (D)
IMD_LED_ON: R8.2, U1.16 (PA2), U$2.1 (G)
unnamed: POWER.A, R5.1
unnamed: C14.1, R16.1
unnamed: C15.1, R18.1
PRECHARGE_COMPLETE: U1.20 (PA4), U$5.1 (G)
PRECHARGE_LED_ON: I/O.8, R4.1, U$5.3 (D)
RESET: JP2.1, R12.1, U1.7 (NRST)
SWCLK: JP2.4, U1.37 (PC6)
SWDIO: JP2.3, U1.34 (PB13)
TC_ON/OFF: I/O.2, R9.1, U1.25 (PC5)
VBAT: U1.1 (VBAT)

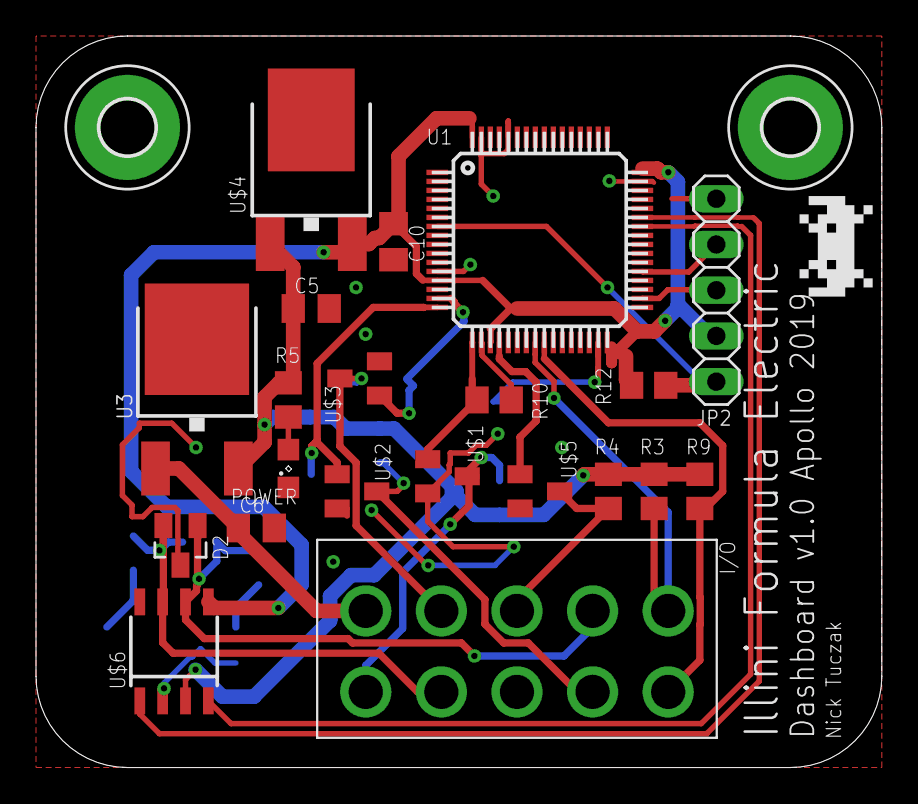
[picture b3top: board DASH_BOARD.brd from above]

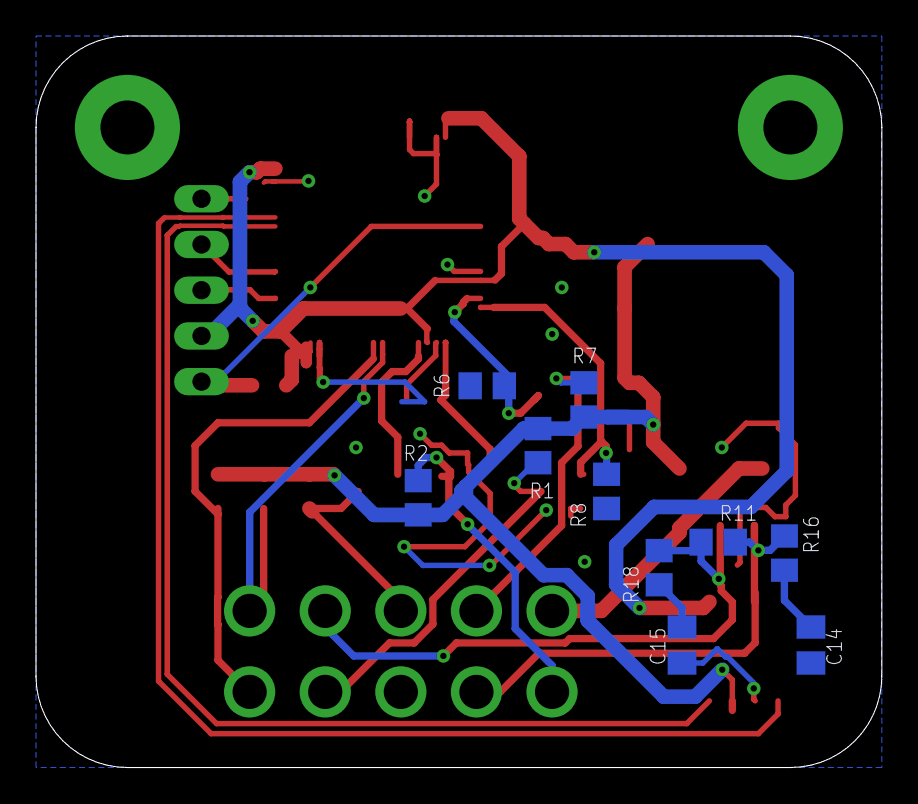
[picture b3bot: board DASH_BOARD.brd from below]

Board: 2 copper layers, 47.0 x 40.6 mm, 33 parts (10 on the bottom side), 24 nets.

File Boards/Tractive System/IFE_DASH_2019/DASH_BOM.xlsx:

Qty | Value | Device | Package | Parts | Description | Column1 | _1
1 |  | PINHD-1X5 | 1X05 | JP2 | PIN HEADER
2 | 10u | C-EUC0805K | C0805K | C5, C10 | CAPACITOR, European symbol
1 | 2.2u | C-EUC0805K | C0805K | C6 | CAPACITOR, European symbol
2 | 100 | R-US_R0805 | R0805 | R16, R18 | RESISTOR, American symbol
10 | 10k | R-US_R0805 | R0805 | R1, R2, R3, R4, R6, R7, R8, R9, R10, R12 | RESISTOR, American symbol
1 | 120 | R-US_R0805 | R0805 | R11 | RESISTOR, American symbol
1 | 3.3V Blue | LEDSML0805 | SML0805 | POWER | LED
1 | 330 | R-US_R0805 | R0805 | R5 | RESISTOR, American symbol
2 | 560p | C-EUC0805K | C0805K | C14, C15 | CAPACITOR, European symbol
4 | DMN2300U | DMN2300U | SOT23 | U$1, U$2, U$3, U$5 | 20V N-Channel Mosfet SOT23
1 | LM2931_FIXED | LM2931_FIXED | DPAK | U$4 | LDO regulator with reverse battery protection- very durable!
1 | MC7805BDD | MC7805BDD | DPAK | U3
1 | MCP2562 | MCP2562 | SOIC8 | U$6 | MCP2562 High Speed CAN Tranceiver
1 | MINIFIT_JR_5566-10 | MINIFIT_JR_5566-10 | MINIFIT_JR_5566-10 | I/O | Molex Minifit JR 5566-10
2 | MOUNT-PAD-ROUND3.0 | MOUNT-PAD-ROUND3.0 | 3,0-PAD | H5, H6 | MOUNTING PAD, round
1 | PESD1CAN | PESD1CAN | SOT23 | D2 | CAN bus ESD protection diode
1 | STM32F10XRXT6 | STM32F10XRXT6 | TQFP64 | U1 | STM32F101/103 64pin LQFP

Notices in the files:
parts and their libraries:
SparkFun-DiscreteSemi: Licensing: Creative Commons ShareAlike 4.0 International - https://creativecommons.org/licenses/by-sa/4.0
